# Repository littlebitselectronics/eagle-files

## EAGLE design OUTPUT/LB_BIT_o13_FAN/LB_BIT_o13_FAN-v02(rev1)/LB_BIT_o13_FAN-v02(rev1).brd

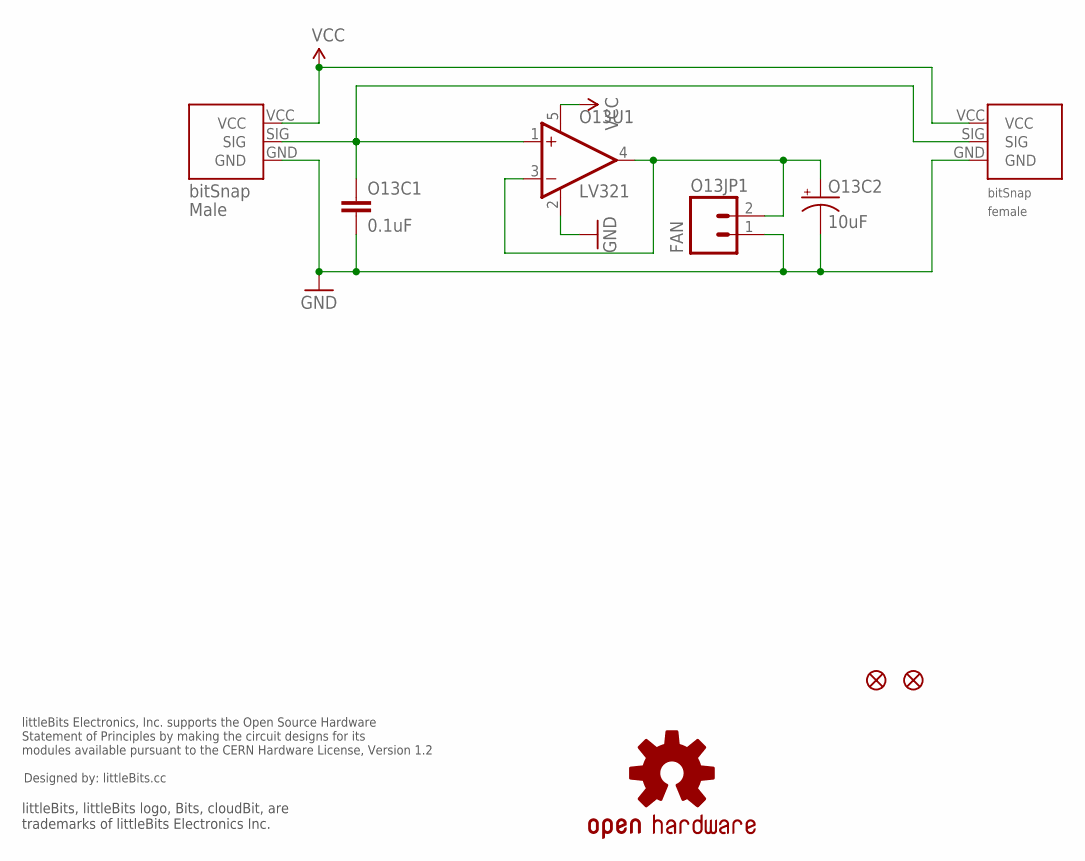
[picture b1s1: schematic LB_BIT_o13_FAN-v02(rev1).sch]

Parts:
JP2, JP3: FIDUCIAL1X2; FIDUCIAL-1X2
O13BSF: BITSNAP_FEMALE
O13BSM: BITSNAP_MALE
O13C1: 0.1uF; 0603-CAP
O13C2: 10uF; EIA3216
O13JP1: FAN; 1X02
O13U1: LV321; SC70-5
U$1: OSHWCREDIT
U$5: OSHW-LOGOL; OSHW-LOGO-L

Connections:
GND: O13BSF.GND, O13BSM.GND, O13C1.2, O13C2.C (-), O13JP1.1, O13U1.2 (V-)
unnamed: O13C2.A (+), O13JP1.2, O13U1.3 (-IN), O13U1.4 (OUT)
SIG: O13BSF.SIG, O13BSM.SIG, O13C1.1, O13U1.1 (+IN)
VCC: O13BSF.VCC, O13BSM.VCC, O13U1.5 (V+)

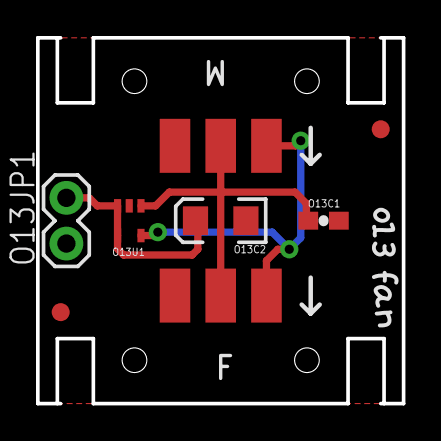
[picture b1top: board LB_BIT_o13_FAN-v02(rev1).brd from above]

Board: 2 copper layers, 20.3 x 20.3 mm, 17 parts (0 on the bottom side), 4 nets.

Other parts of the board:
U$2: O
U$3: 1
U$6: OSHW_FILLX150_NOTEXT
U$7: 3
U$8: F
U$9: A
U$10: N

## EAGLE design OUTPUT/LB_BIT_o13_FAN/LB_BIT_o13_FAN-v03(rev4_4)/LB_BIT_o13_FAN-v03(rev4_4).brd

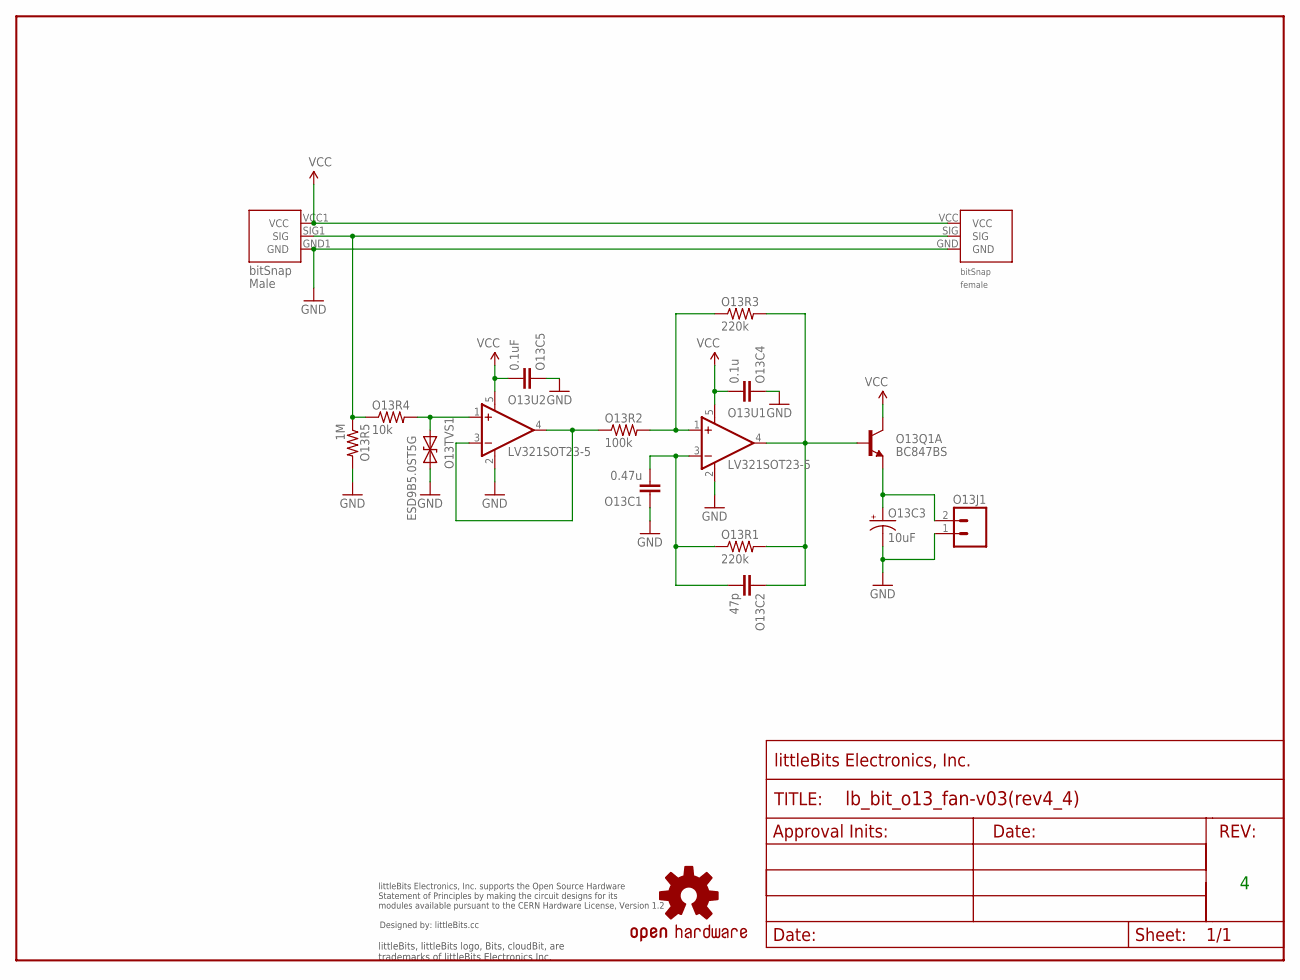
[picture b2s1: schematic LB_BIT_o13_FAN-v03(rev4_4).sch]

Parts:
O13BSF1: BITSNAP_V03_FEMALE
O13BSM1: BITSNAP_V03_MALE
O13C1: 0.47u; CAP-0603
O13C2: 47p; CAP-0603
O13C3: 10uF; EIA3216
O13C4: 0.1u; CAP-0603
O13C5: 0.1uF; CAP-0603
O13J1: HDR-2JST-2-SMD; JST-2-SMD
O13Q1: BC847BS; SOT-363_PHILLIPS
O13R1, O13R3: 220k; RES-0603
O13R2: 100k; RES-0603
O13R4: 10k; RES-0603
O13R5: 1M; RES-0603
O13TVS1: ESD9B5.0ST5G; SOD-923
O13U1, O13U2: LV321SOT23-5; SOT23-5
U$1: OSHWCREDIT
U$2: FRAME-LETTER-OHWOHW; FABDWG01-OHW
U$3: OSHW-LOGOL; OSHW-LOGO-L

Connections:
GND: O13BSF1.GND, O13BSM1.GND1 (GND), O13C1.1, O13C3.-, O13C4.1, O13C5.1, O13J1.1, O13R5.2, O13TVS1.1 (A), O13U1.2 (V-), O13U2.2 (V-)
unnamed: O13R2.2, O13R3.1, O13U1.1 (+IN)
unnamed: O13R2.1, O13U2.3 (-IN), O13U2.4 (OUT)
unnamed: O13C3.+, O13J1.2, O13Q1.1 (E)
unnamed: O13C1.2, O13C2.2, O13R1.1, O13U1.3 (-IN)
unnamed: O13R4.2, O13TVS1.2 (C), O13U2.1 (+IN)
unnamed: O13C2.1, O13Q1.2 (B), O13R1.2, O13R3.2, O13U1.4 (OUT)
SIG: O13BSF1.SIG, O13BSM1.SIG1 (SIG), O13R4.1, O13R5.1
VCC: O13BSF1.VCC, O13BSM1.VCC1 (VCC), O13C4.2, O13C5.2, O13Q1.6 (C), O13U1.5 (V+), O13U2.5 (V+)

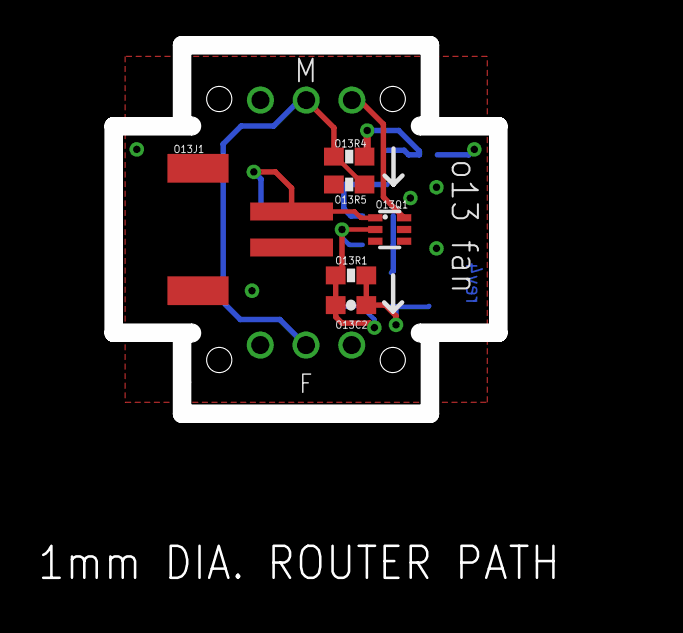
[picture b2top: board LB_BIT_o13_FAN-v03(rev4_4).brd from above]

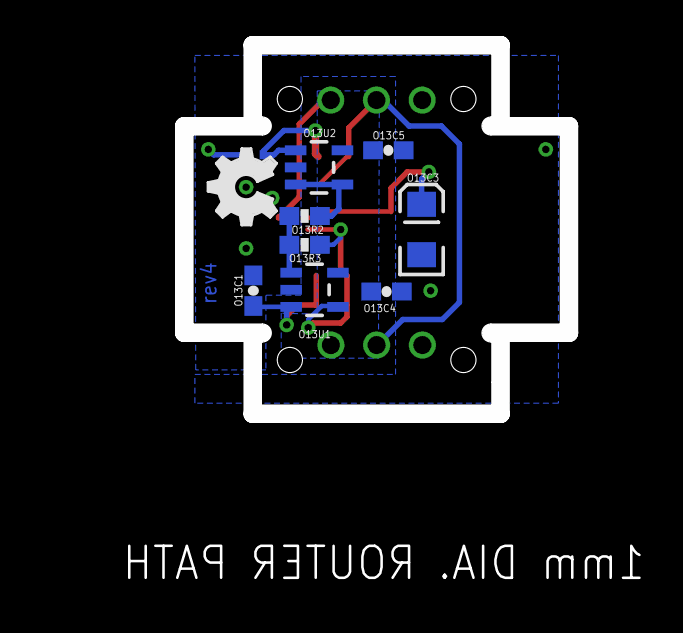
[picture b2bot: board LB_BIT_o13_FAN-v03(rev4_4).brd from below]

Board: 2 copper layers, 21.4 x 20.5 mm, 21 parts (9 on the bottom side), 9 nets.

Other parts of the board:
U$6: OSHW_FILLX150_NOTEXT

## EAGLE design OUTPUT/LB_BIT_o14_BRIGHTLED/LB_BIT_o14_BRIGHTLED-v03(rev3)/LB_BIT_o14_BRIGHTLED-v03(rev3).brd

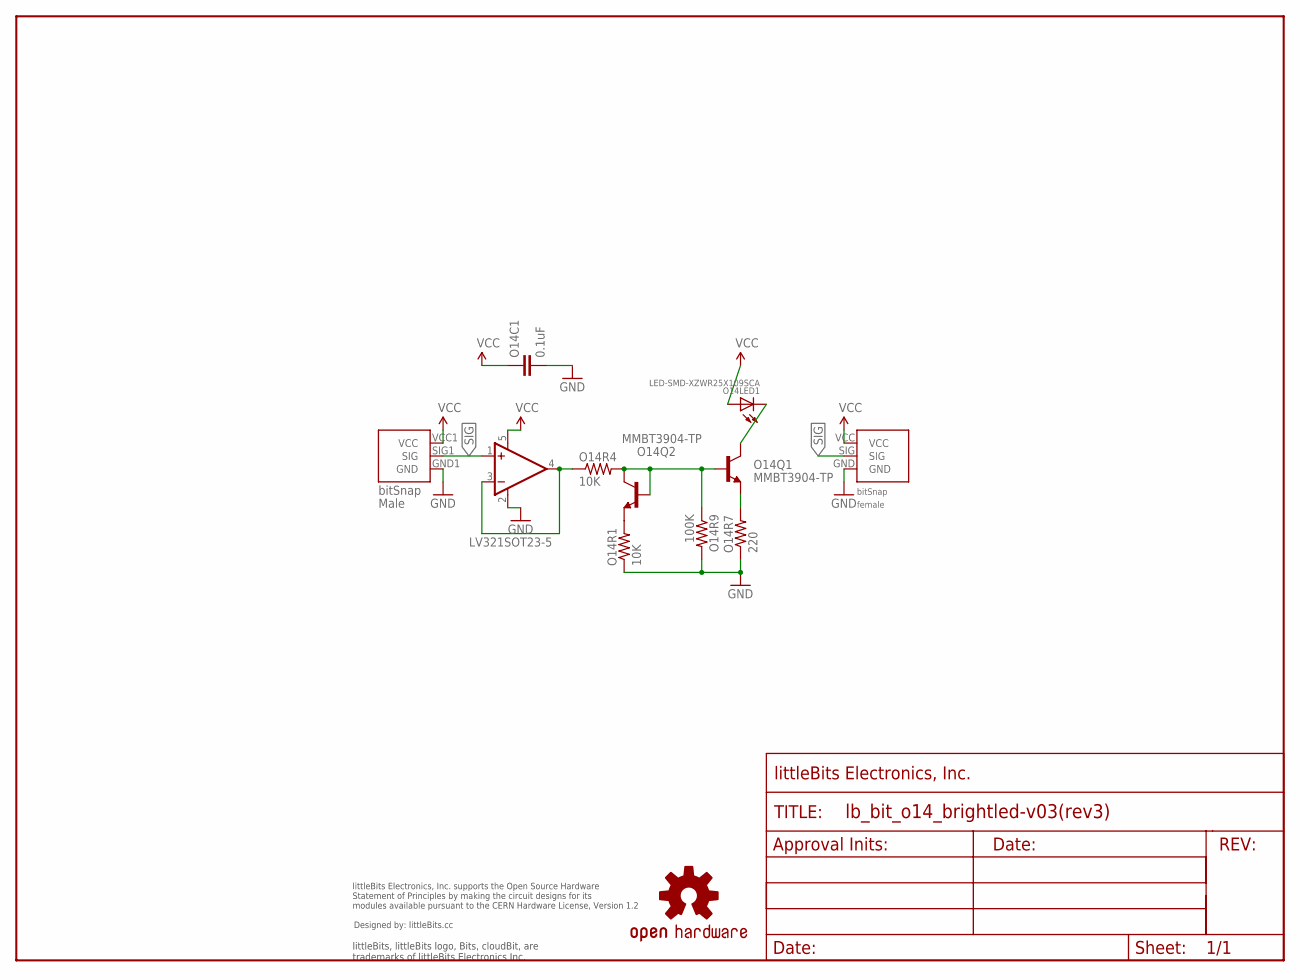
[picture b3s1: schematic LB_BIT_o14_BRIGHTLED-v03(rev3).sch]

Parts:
O14BSF1: BITSNAP_V03_FEMALE
O14BSM1: BITSNAP_V03_MALE
O14C1: 0.1uF; 0603-CAP
O14LED1: LED-SMD-XZWR25X109SCA
O14Q1, O14Q2: MMBT3904-TP; SOT23
O14R1, O14R4: 10K; 0603-RES
O14R7: 220; 0603-RES
O14R9: 100K; 0603-RES
O14U2: LV321SOT23-5; SOT23-5
U$1: OSHWCREDIT
U$6: OSHW-LOGOL; OSHW-LOGO-L
U$16: FRAME-LETTER-OHWOHW; FABDWG01-OHW

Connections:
GND: O14BSF1.GND, O14BSM1.GND1 (GND), O14C1.2, O14R1.1, O14R7.1, O14R9.2, O14U2.2 (V-)
unnamed: O14Q1.1 (B), O14Q2.1 (B), O14Q2.3 (C), O14R4.2, O14R9.1
unnamed: O14Q1.2 (E), O14R7.2
unnamed: O14Q2.2 (E), O14R1.2
unnamed: O14R4.1, O14U2.3 (-IN), O14U2.4 (OUT)
SIG: O14BSF1.SIG, O14BSM1.SIG1 (SIG), O14U2.1 (+IN)
THERMAL: O14LED1.C, O14Q1.3 (C)
VCC: O14BSF1.VCC, O14BSM1.VCC1 (VCC), O14C1.1, O14LED1.A, O14U2.5 (V+)

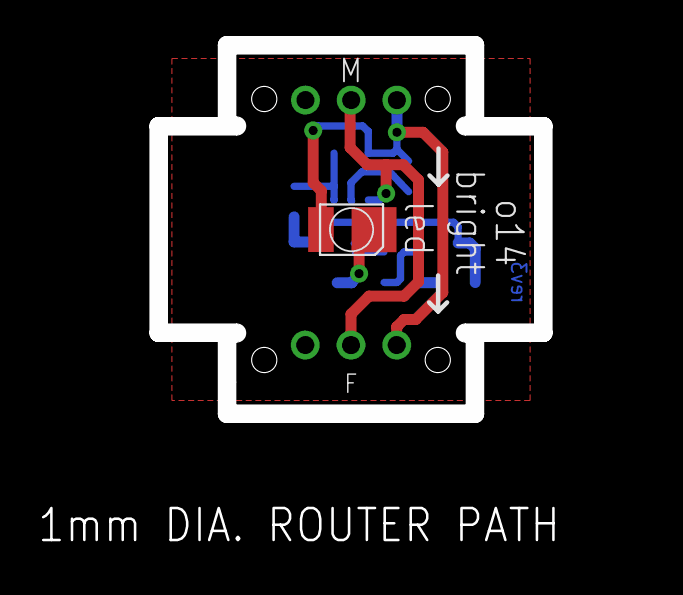
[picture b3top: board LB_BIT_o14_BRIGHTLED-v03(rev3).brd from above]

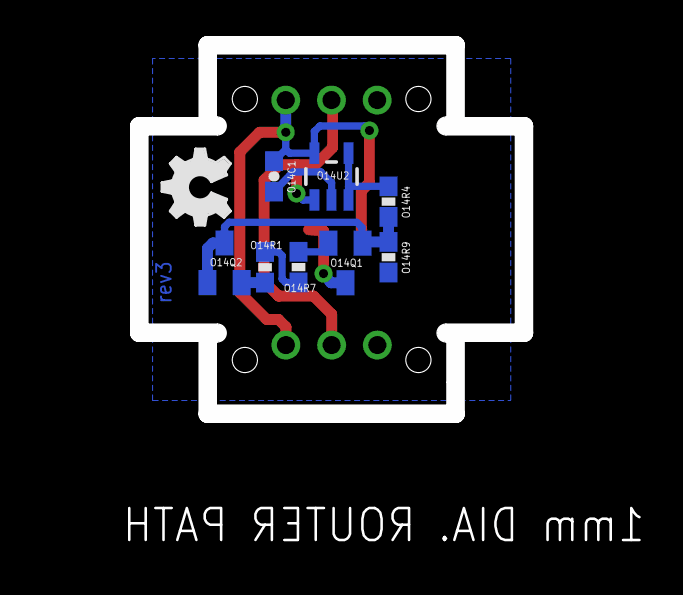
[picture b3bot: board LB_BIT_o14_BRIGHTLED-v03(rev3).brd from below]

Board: 2 copper layers, 21.4 x 20.5 mm, 15 parts (8 on the bottom side), 8 nets.

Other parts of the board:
U$2: OSHW_FILLX150_NOTEXT

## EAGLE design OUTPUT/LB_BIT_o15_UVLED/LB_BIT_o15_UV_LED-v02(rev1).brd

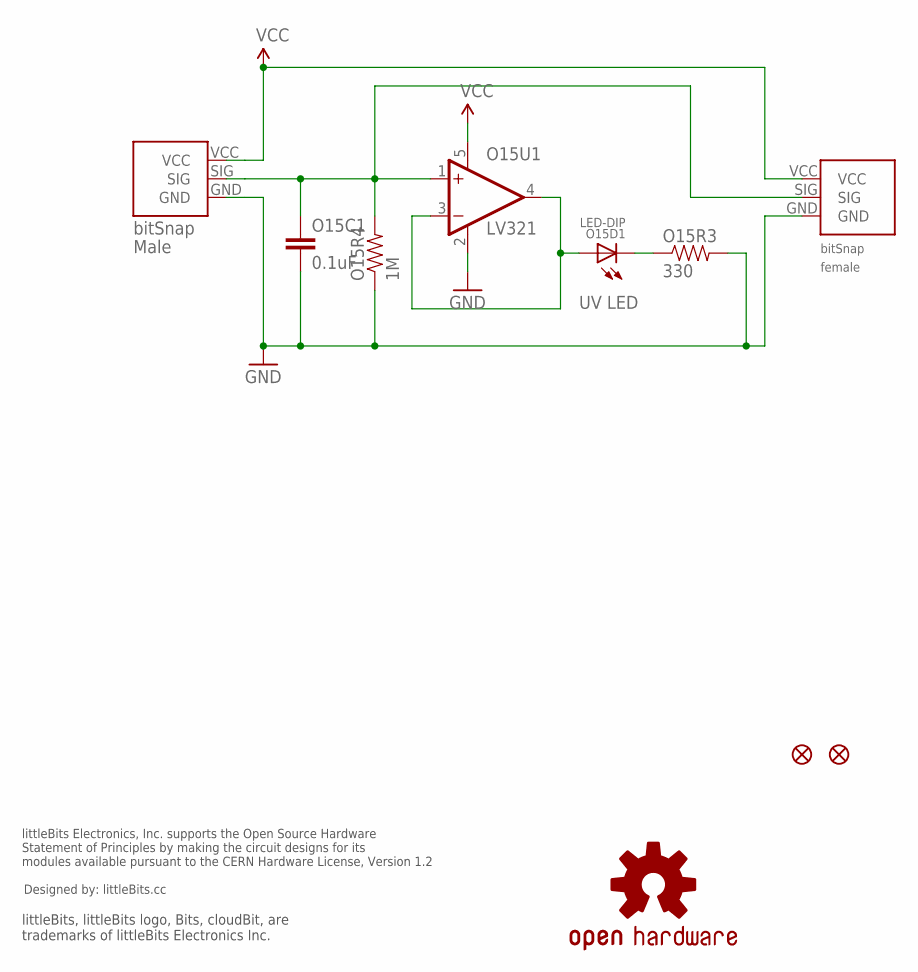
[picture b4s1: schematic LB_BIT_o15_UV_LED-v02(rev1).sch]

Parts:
O15BSF: BITSNAP_FEMALE
O15BSM: BITSNAP_MALE
O15C1: 0.1uF; 0603-CAP
O15D1: LED-DIP
O15FD1, O15FD2: FIDUCIAL1X2.5; FIDUCIAL-1X2.5
O15R3: 330; 0603-RES
O15R4: 1M; 0603-RES
O15U1: LV321; SC70-5
U$1: OSHWCREDIT
U$3: OSHW-LOGOL; OSHW-LOGO-L

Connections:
GND: O15BSF.GND, O15BSM.GND, O15C1.2, O15R3.2, O15R4.1, O15U1.2 (V-)
LEDGND: O15D1.C, O15R3.1
unnamed: O15D1.A, O15U1.3 (-IN), O15U1.4 (OUT)
SIG: O15BSF.SIG, O15BSM.SIG, O15C1.1, O15R4.2, O15U1.1 (+IN)
VCC: O15BSF.VCC, O15BSM.VCC, O15U1.5 (V+)

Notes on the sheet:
UV LED

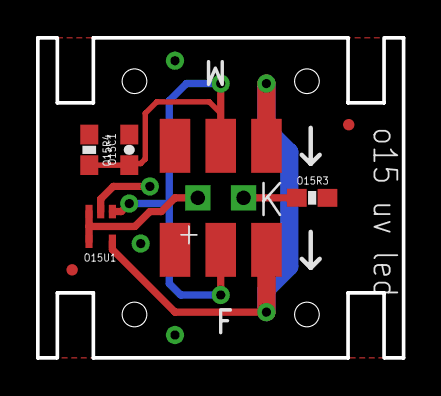
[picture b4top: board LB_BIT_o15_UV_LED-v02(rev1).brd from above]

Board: 2 copper layers, 20.3 x 17.8 mm, 13 parts (0 on the bottom side), 5 nets.

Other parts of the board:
U$6: OSHW_FILLX150_NOTEXT
U$7: CC_TEXT
U$8: LB_V02

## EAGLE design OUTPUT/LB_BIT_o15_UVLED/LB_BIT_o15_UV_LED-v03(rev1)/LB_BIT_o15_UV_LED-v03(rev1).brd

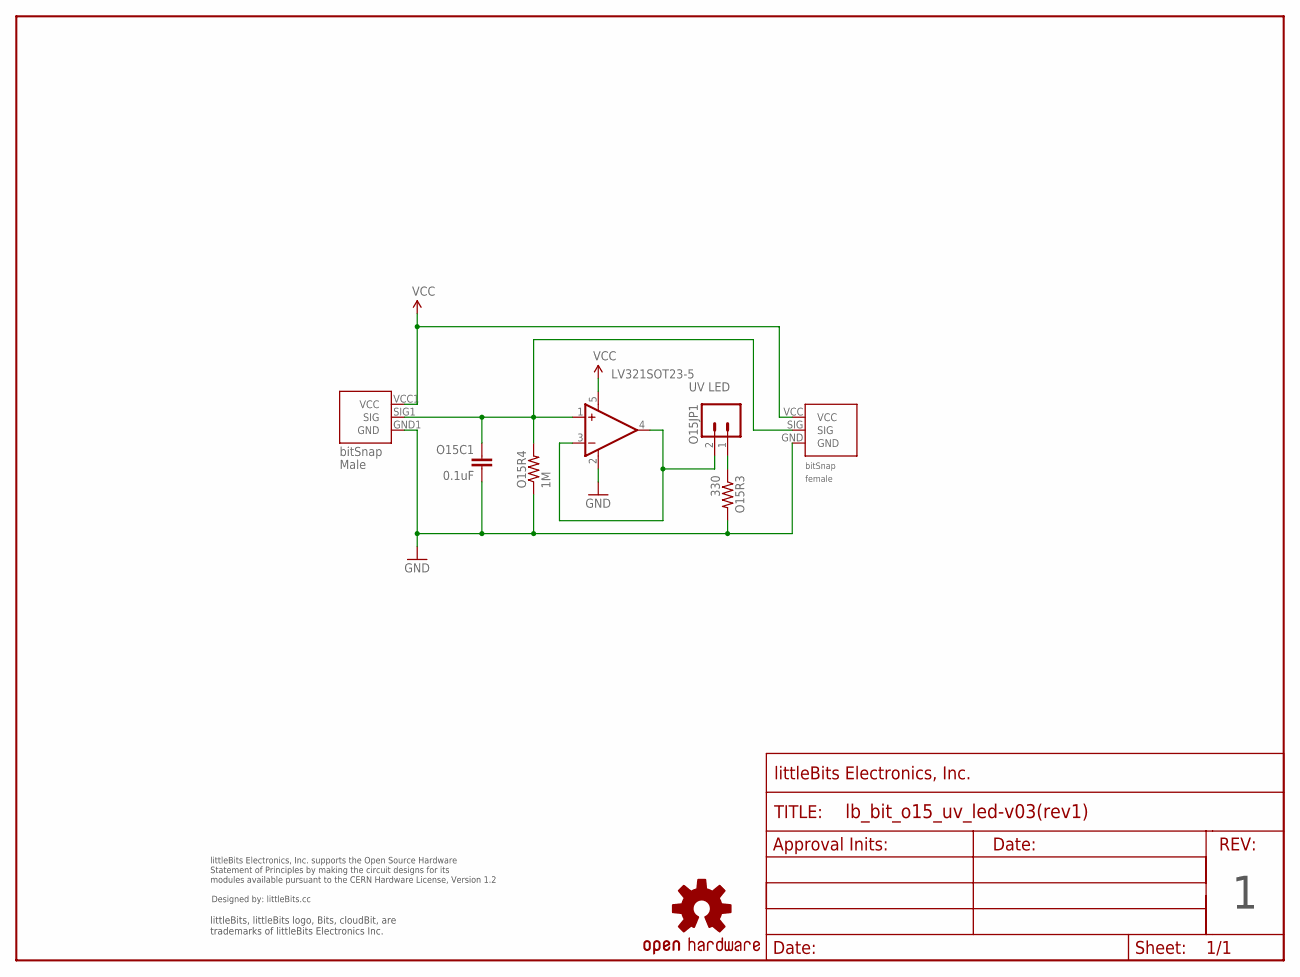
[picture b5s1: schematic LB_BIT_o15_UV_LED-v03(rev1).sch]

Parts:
O15BSF1: BITSNAP_V03_FEMALE
O15BSM1: BITSNAP_V03_MALE
O15C1: 0.1uF; 0603-CAP
O15JP1: M02-JST-2MM-SMT; S2B-PH
O15R3: 330; 0603-RES
O15R4: 1M; 0603-RES
O15U1: LV321SOT23-5; SOT23-5
U$1: FRAME-LETTER-OHWOHW; FABDWG01-OHW
U$3: OSHW-LOGOL; OSHW-LOGO-L
U$4: OSHWCREDIT

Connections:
GND: O15BSF1.GND, O15BSM1.GND1 (GND), O15C1.2, O15R3.2, O15R4.1, O15U1.2 (V-)
unnamed: O15JP1.2, O15U1.3 (-IN), O15U1.4 (OUT)
unnamed: O15JP1.1, O15R3.1
SIG: O15BSF1.SIG, O15BSM1.SIG1 (SIG), O15C1.1, O15R4.2, O15U1.1 (+IN)
VCC: O15BSF1.VCC, O15BSM1.VCC1 (VCC), O15U1.5 (V+)

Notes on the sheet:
UV LED

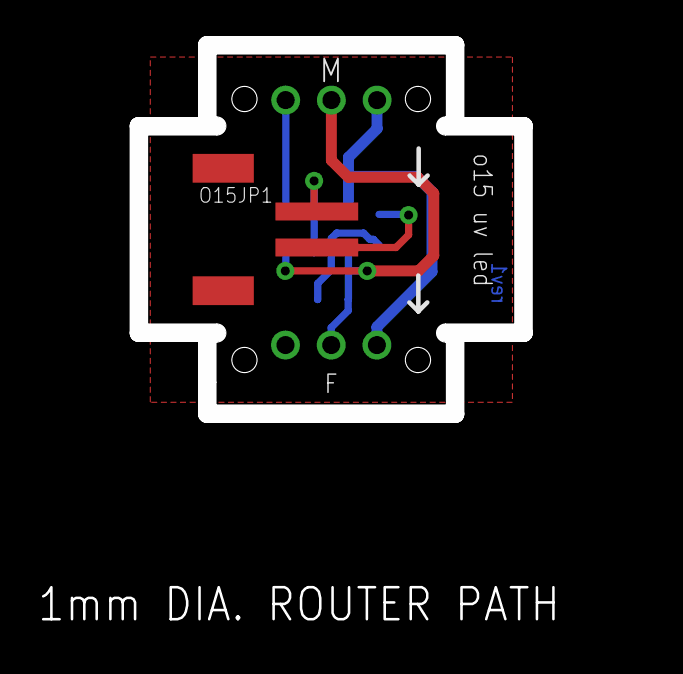
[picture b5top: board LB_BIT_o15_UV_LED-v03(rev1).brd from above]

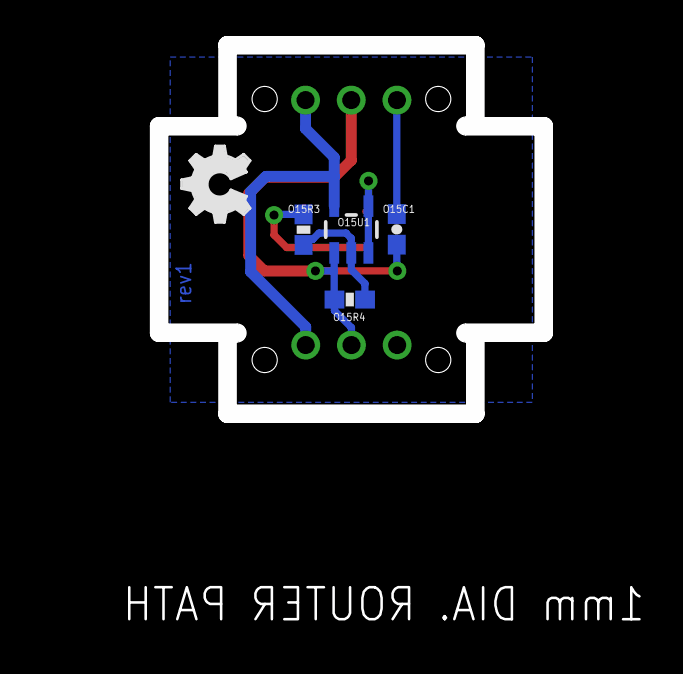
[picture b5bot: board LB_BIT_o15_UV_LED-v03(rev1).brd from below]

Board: 2 copper layers, 21.4 x 20.5 mm, 11 parts (4 on the bottom side), 5 nets.

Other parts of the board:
U$6: OSHW_FILLX150_NOTEXT

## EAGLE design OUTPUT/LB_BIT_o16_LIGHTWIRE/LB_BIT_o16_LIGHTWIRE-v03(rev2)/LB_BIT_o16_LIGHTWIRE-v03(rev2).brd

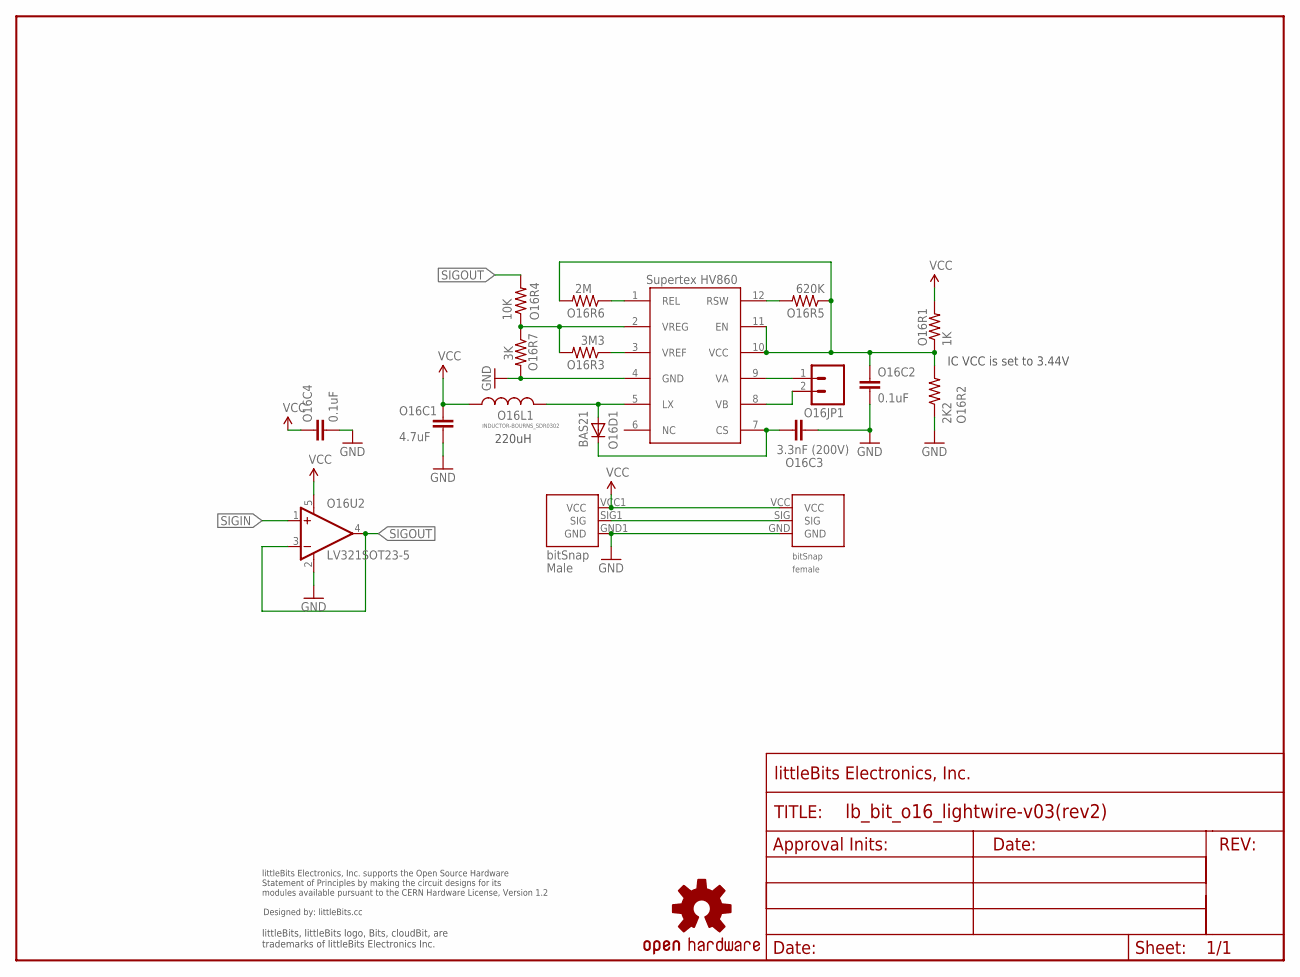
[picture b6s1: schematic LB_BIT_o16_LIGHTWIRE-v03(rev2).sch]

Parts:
O16BSF1: BITSNAP_V03_FEMALE
O16BSM1: BITSNAP_V03_MALE
O16C1: 4.7uF; 0603-CAP
O16C2, O16C4: 0.1uF; 0603-CAP
O16C3: 3.3nF (200V); 0805
O16D1: BAS21; SOD-323
O16JP1: M02-JST-2MM-SMT; S2B-PH
O16L1: INDUCTOR-BOURNS_SDR0302
O16R1: 1K; 0603-RES
O16R2: 2K2; 0603-RES
O16R3: 3M3; 0603-RES
O16R4: 10K; 0603-RES
O16R5: 620K; 0603-RES
O16R6: 2M; 0603-RES
O16R7: 3K; 0603-RES
O16U1: SUPERTEX-HV860; QFN-12(K7)
O16U2: LV321SOT23-5; SOT23-5
U$1: OSHW-LOGOL; OSHW-LOGO-L
U$2: OSHWCREDIT
U$5: FRAME-LETTER-OHWOHW; FABDWG01-OHW

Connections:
GND: O16BSF1.GND, O16BSM1.GND1 (GND), O16C1.2, O16C2.2, O16C3.2, O16C4.2, O16R2.1, O16R7.2, O16U1.4 (GND), O16U2.2 (V-)
unnamed: O16JP1.1, O16U1.9 (VA)
unnamed: O16C3.1, O16D1.1 (C), O16U1.7 (CS)
unnamed: O16JP1.2, O16U1.8 (VB)
unnamed: O16R3.1, O16U1.3 (VREF)
unnamed: O16D1.2 (A), O16L1.2, O16U1.5 (LX)
unnamed: O16R6.1, O16U1.1 (REL)
unnamed: O16R5.2, O16U1.12 (RSW)
SIGIN: O16BSF1.SIG, O16BSM1.SIG1 (SIG), O16U2.1 (+IN)
SIGOUT: O16R4.2, O16U2.3 (-IN), O16U2.4 (OUT)
VCC: O16BSF1.VCC, O16BSM1.VCC1 (VCC), O16C1.1, O16C4.1, O16L1.1, O16R1.2, O16U2.5 (V+)
VIN: O16C2.1, O16R1.1, O16R2.2, O16R5.1, O16R6.2, O16U1.10 (VCC), O16U1.11 (EN)
VREG: O16R3.2, O16R4.1, O16R7.1, O16U1.2 (VREG)

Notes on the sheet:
IC VCC is set to 3.44V
220uH
Supertex HV860

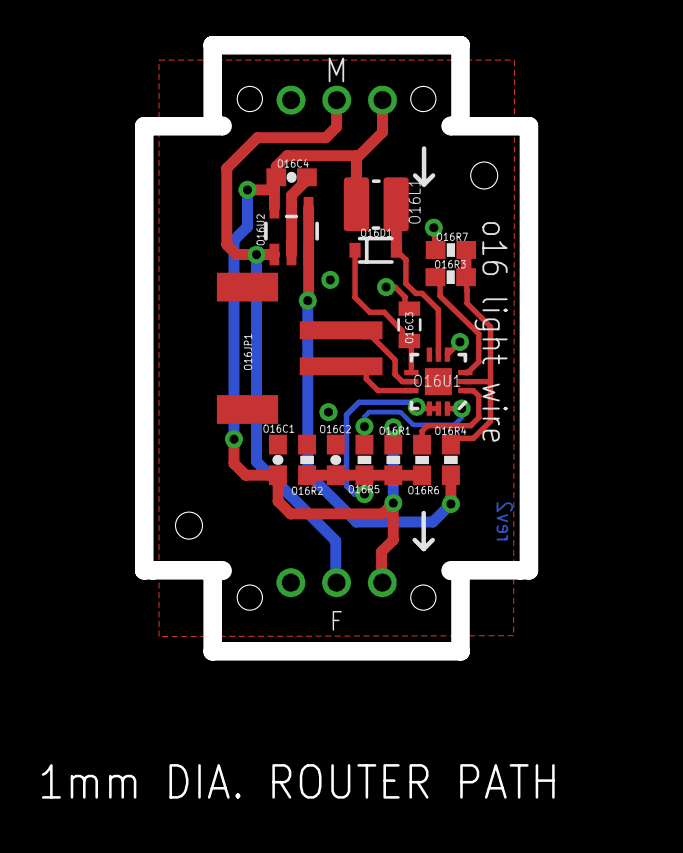
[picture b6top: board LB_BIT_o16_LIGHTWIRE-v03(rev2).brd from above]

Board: 2 copper layers, 21.4 x 33.7 mm, 22 parts (0 on the bottom side), 13 nets.

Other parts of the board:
U$6: OSHW_FILLX150_NOTEXT

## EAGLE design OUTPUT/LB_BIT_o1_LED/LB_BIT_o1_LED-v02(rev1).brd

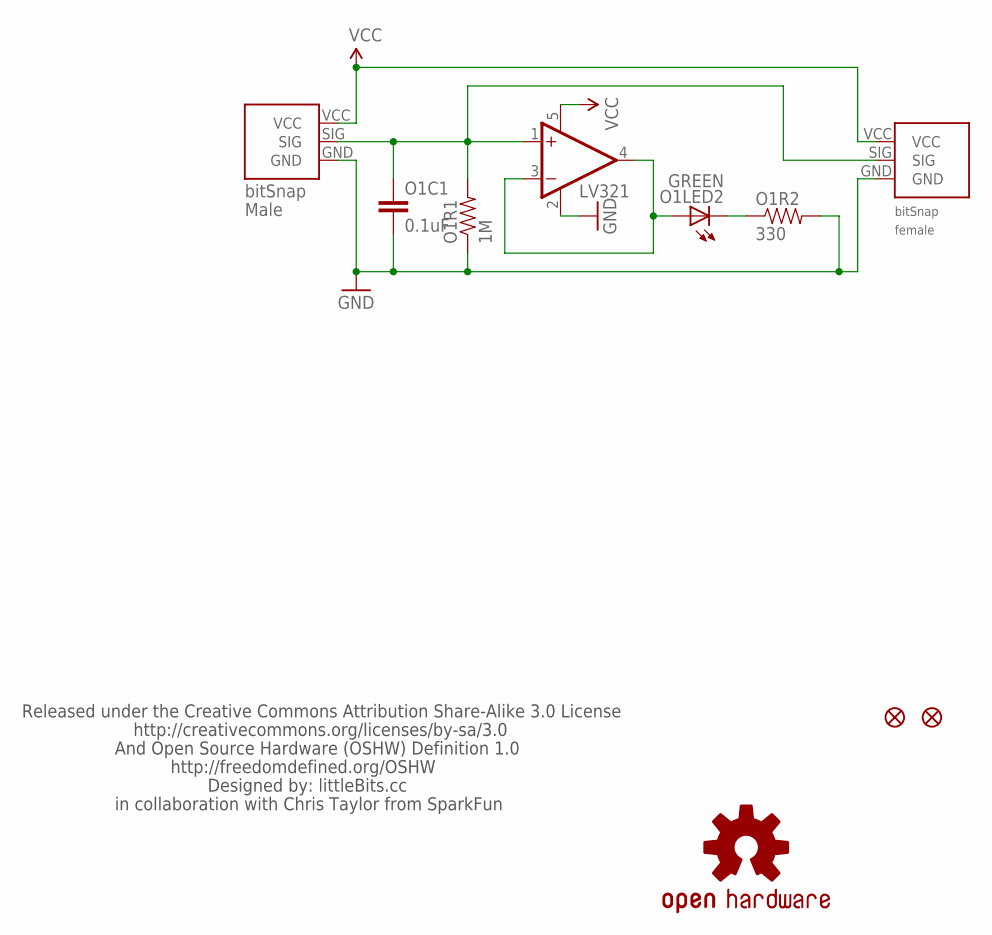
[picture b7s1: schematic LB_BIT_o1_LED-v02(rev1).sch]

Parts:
JP1, JP2: FIDUCIAL1X2.5; FIDUCIAL-1X2.5
O1BSF: BITSNAP_FEMALE
O1BSM: BITSNAP_MALE
O1C1: 0.1uF; 0603-CAP
O1LED2: GREEN; LED-1206
O1R1: 1M; 0603-RES
O1R2: 330; 0603-RES
O1U1: LV321; SC70
U$1: LB_CREDITS; OSHWCREDIT
U$3: OSHW-LOGOL; OSHW-LOGO-L

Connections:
GND: O1BSF.GND, O1BSM.GND, O1C1.2, O1R1.1, O1R2.2, O1U1.2 (V-)
LEDGND: O1LED2.C, O1R2.1
unnamed: O1LED2.A, O1U1.3 (-IN), O1U1.4 (OUT)
SIG: O1BSF.SIG, O1BSM.SIG, O1C1.1, O1R1.2, O1U1.1 (+IN)
VCC: O1BSF.VCC, O1BSM.VCC, O1U1.5 (V+)

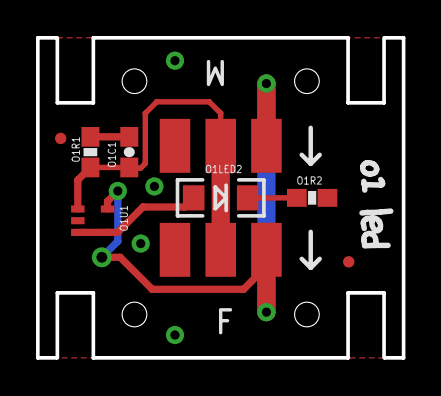
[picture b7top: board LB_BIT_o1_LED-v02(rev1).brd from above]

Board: 2 copper layers, 20.3 x 17.8 mm, 12 parts (0 on the bottom side), 5 nets.

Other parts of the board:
U$2: OSHW_FILLX150_NOTEXT

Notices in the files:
parts and their libraries:
LITTLEBITS: modules available pursuant to the CERN Hardware License,
Version 1.2
SparkFun_NEW: Licensing: CC v3.0 Share-Alike You are welcome to use this library for commercial purposes.
LITTLEBITS: modules available pursuant to the CERN Hardware License, Version 1.2
